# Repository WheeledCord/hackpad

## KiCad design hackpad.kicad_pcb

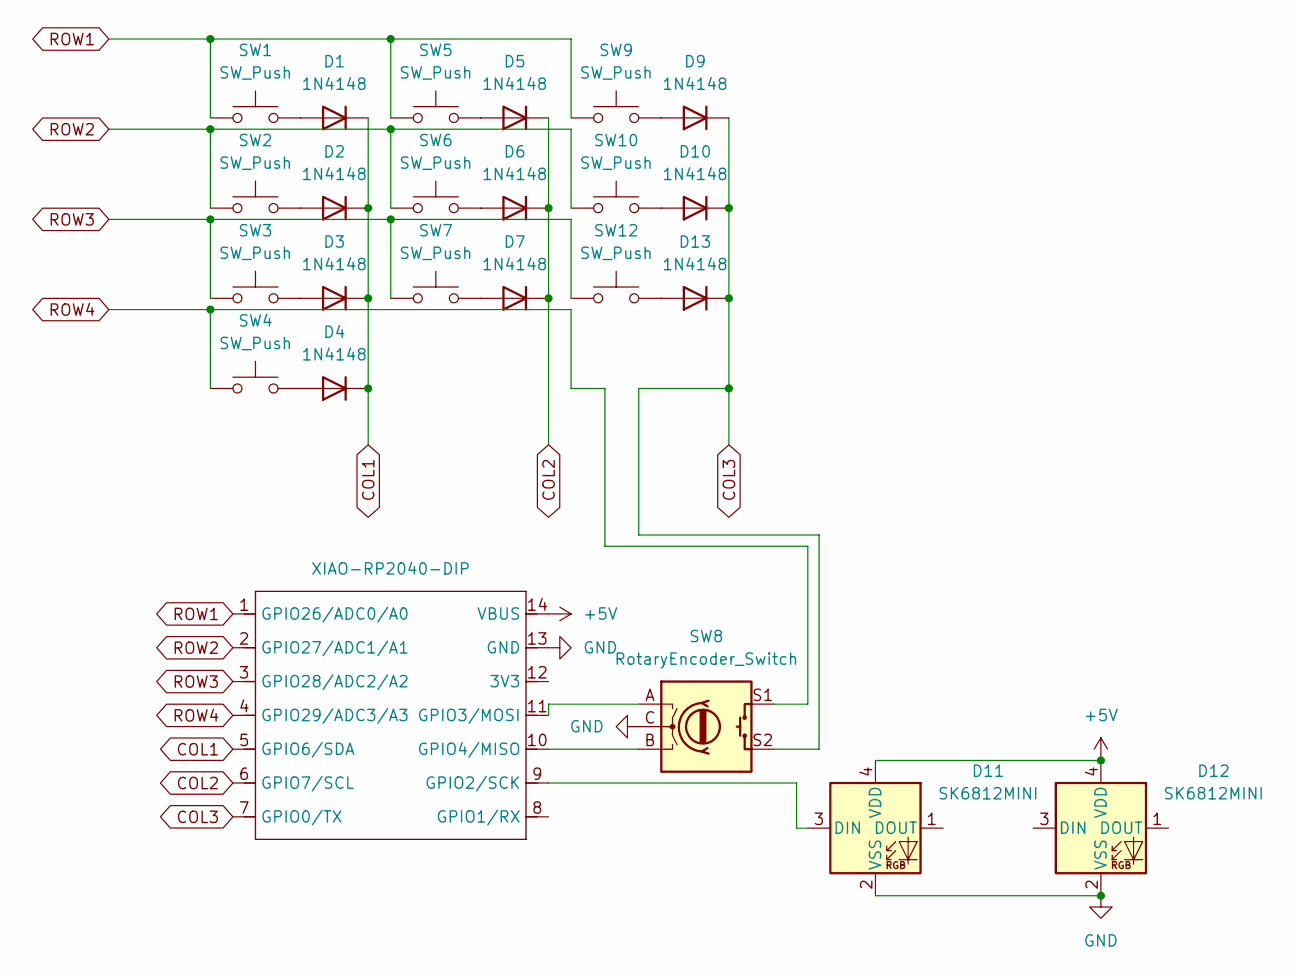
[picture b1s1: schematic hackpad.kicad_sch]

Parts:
D1, D2, D3, D4, D5, D6, D7, D9, D10, D13: 1N4148; D_DO-35_SOD27_P7.62mm_Horizontal
D11, D12: SK6812MINI; LED_SK6812MINI_PLCC4_3.5x3.5mm_P1.75mm
SW1, SW2, SW3, SW4, SW5, SW6, SW7, SW9, SW10, SW12: SW_Push; SW_Cherry_MX_1.00u_PCB
SW8: RotaryEncoder_Switch; RotaryEncoder_Alps_EC11E-Switch_Vertical_H20mm_MountingHoles
U1: XIAO-RP2040-DIP

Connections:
+5V: D11.4 (VDD), D12.4 (VDD), U1.14 (VBUS)
COL1: D1.1 (K), D2.1 (K), D3.1 (K), D4.1 (K), U1.5 (GPIO6/SDA)
COL2: D5.1 (K), D6.1 (K), D7.1 (K), U1.6 (GPIO7/SCL)
COL3: D9.1 (K), D10.1 (K), D13.1 (K), SW8.S2, U1.7 (GPIO0/TX)
GND: D11.2 (VSS), D12.2 (VSS), SW8.C, U1.13 (GND)
unnamed: D1.2 (A), SW1.2
unnamed: D2.2 (A), SW2.2
unnamed: D3.2 (A), SW3.2
unnamed: D4.2 (A), SW4.2
unnamed: D5.2 (A), SW5.2
unnamed: D6.2 (A), SW6.2
unnamed: D7.2 (A), SW7.2
unnamed: D9.2 (A), SW9.2
unnamed: D10.2 (A), SW10.2
unnamed: D11.3 (DIN), U1.9 (GPIO2/SCK)
unnamed: D13.2 (A), SW12.2
unnamed: SW8.A, U1.11 (GPIO3/MOSI)
unnamed: SW8.B, U1.10 (GPIO4/MISO)
ROW1: SW1.1, SW5.1, SW9.1, U1.1 (GPIO26/ADC0/A0)
ROW2: SW2.1, SW6.1, SW10.1, U1.2 (GPIO27/ADC1/A1)
ROW3: SW3.1, SW7.1, SW12.1, U1.3 (GPIO28/ADC2/A2)
ROW4: SW4.1, SW8.S1, U1.4 (GPIO29/ADC3/A3)

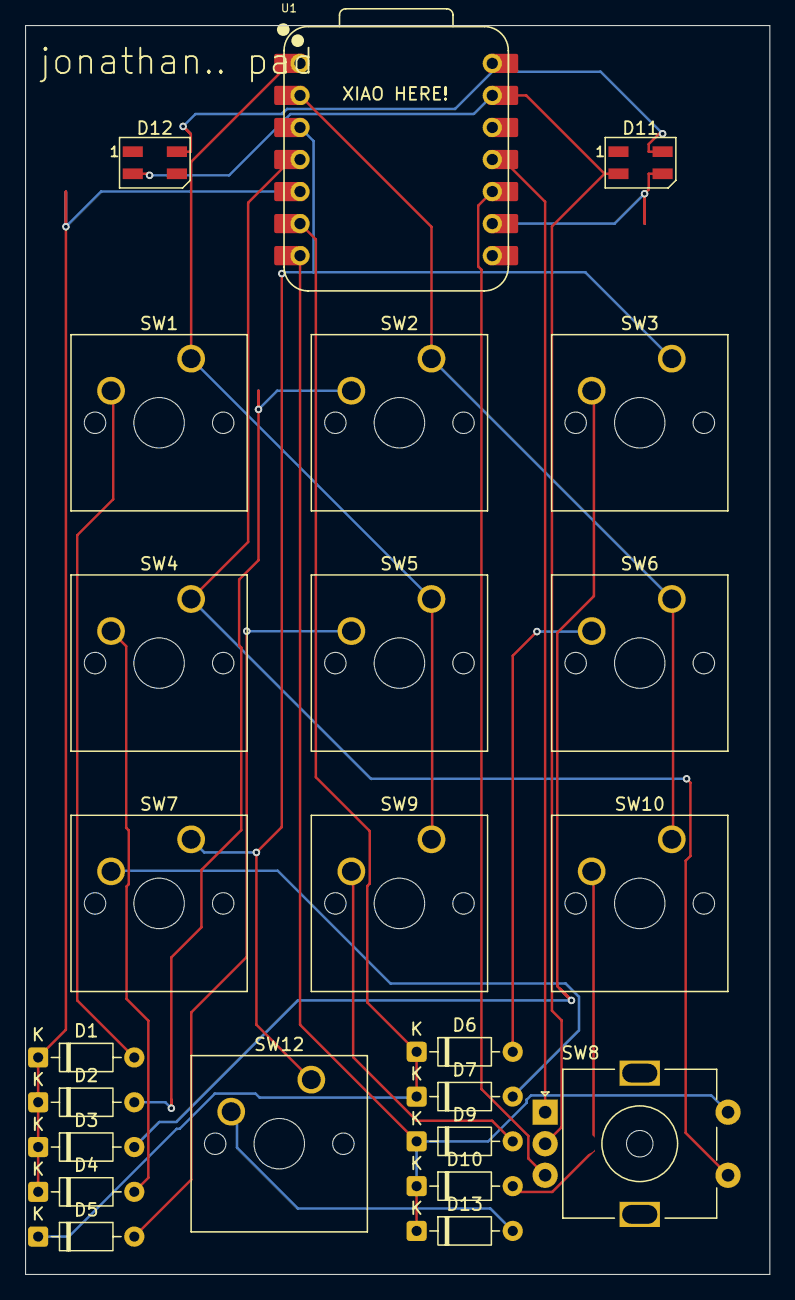
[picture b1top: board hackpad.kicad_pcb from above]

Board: 2 copper layers, 59.0 x 99.0 mm, 24 parts (0 on the bottom side), 22 nets.

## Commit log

2025-05-25 everything
